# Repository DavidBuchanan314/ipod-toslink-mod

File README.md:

# ipod-toslink-mod
Adding optical digital audio output to classic iPods

NOTE: The current PCB files are untested. I am waiting for parts etc. to build and test the first batch, which should hopefully be some time in January 2021.

Update: This doesn't really work due to clock synchronisation issues. There's constant clicking/crackling due to the clock jitter inherent in the LRCLK. Would need additional parts to clean up the signal maybe? Dunno...

# Wiring

There are 5 wires that must be soldered to the iPod motherboard. You will need to scrape the soldermask from the top of the 3 vias before soldering, using a sharp knife.

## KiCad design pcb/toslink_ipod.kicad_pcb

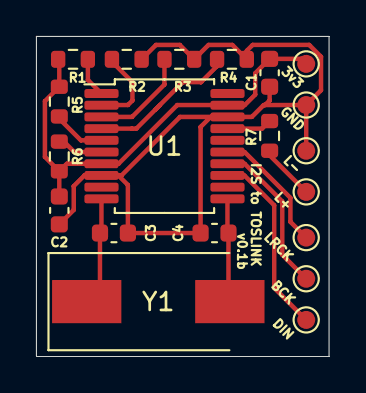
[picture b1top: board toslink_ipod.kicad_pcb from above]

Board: 2 copper layers, 16.3 x 17.8 mm, 20 parts (0 on the bottom side), 15 nets.

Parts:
3v3: TestPoint; TestPoint_Pad_D1.0mm
BCK: TestPoint; TestPoint_Pad_D1.0mm
C1: 1uF; C_0603_1608Metric
C2: 0.1uF; C_0603_1608Metric
C3, C4: 15pF; C_0603_1608Metric
DIN: TestPoint; TestPoint_Pad_D1.0mm
GND: TestPoint; TestPoint_Pad_D1.0mm
L+: TestPoint; TestPoint_Pad_D1.0mm
L-: TestPoint; TestPoint_Pad_D1.0mm
LRCK: TestPoint; TestPoint_Pad_D1.0mm
R1, R2, R3, R4, R5, R6: 10K; R_0603_1608Metric
R7: 220R; R_0603_1608Metric
U1: WM8804; SSOP-20_5.3x7.2mm_P0.65mm
Y1: 22.5792MHz; Crystal_SMD_FOX_FE-2Pin_7.5x5.0mm_HandSoldering

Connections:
+3V3: 3v3.1, C1.1, C2.1, R1.2, R5.2, R6.2, U1.7, U1.19
GND: C1.2, C2.2, C3.2, C4.2, GND.1, L-.1, R2.2, R3.2, R4.2, U1.8, U1.18
unnamed: BCK.1, U1.14
unnamed: C3.1, U1.10, Y1.1
unnamed: C4.1, U1.11, Y1.2
unnamed: DIN.1, U1.13
unnamed: L+.1, R7.1
unnamed: LRCK.1, U1.15
unnamed: R1.1, U1.1
unnamed: R2.1, U1.2
unnamed: R3.1, U1.3
unnamed: R4.1, U1.4
unnamed: R5.1, U1.5
unnamed: R6.1, U1.6
unnamed: R7.2, U1.17

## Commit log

2020-12-20 Add some useful datasheets
2020-12-21 v0.1 PCB design files
2020-12-21 Add motherboard image
2020-12-21 Flip C1 for shorter traces
